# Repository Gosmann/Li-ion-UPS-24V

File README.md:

# Li-ion-UPS-24V

24V-input 24V-out lithium ion uninterruptible power supply

24V -> BUCK LM2596 -> 5V

5V -> Li-ion charger -> 3.7V

3.7V -> BOOST MT3608 -> 24V

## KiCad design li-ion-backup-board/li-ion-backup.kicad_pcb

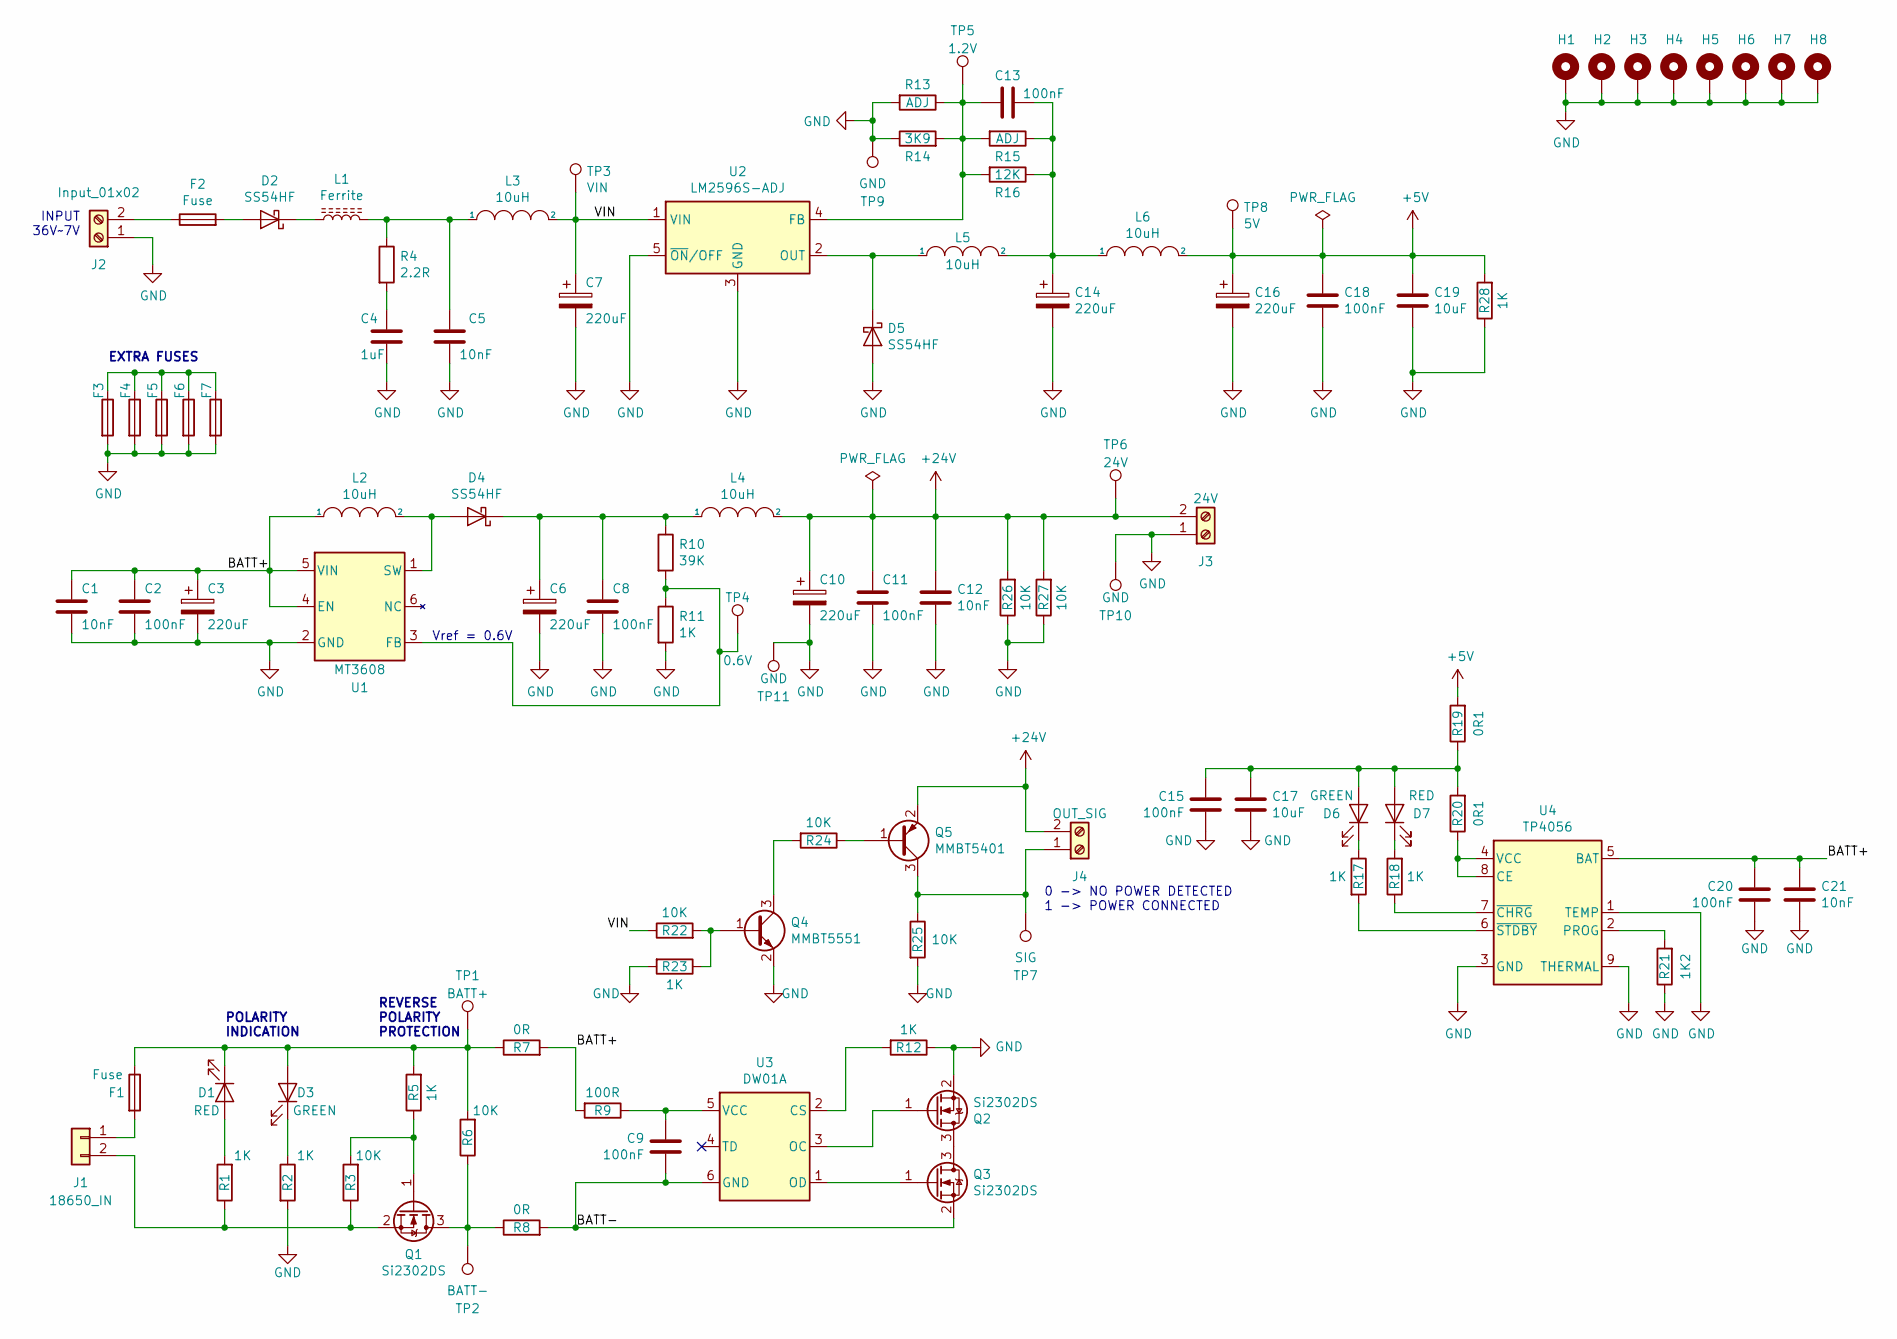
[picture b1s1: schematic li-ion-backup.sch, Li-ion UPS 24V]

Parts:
C1, C5, C12, C21: 10nF; C_0805_2012Metric; LCSC C1710
C2, C8, C9, C11, C13, C15, C18, C20: 100nF; C_0805_2012Metric; Voltage 50V; LCSC C49678
C3, C6, C7, C10, C14, C16: 220uF; CP_Elec_8x10; Voltage 35V; LCSC C311611
C4: 1uF; C_0805_2012Metric; LCSC C28323
C17, C19: 10uF; C_0805_2012Metric; Voltage 25V; LCSC C15850
D1, D7: RED; LED_0805_2012Metric; LCSC C84256
D2, D4, D5: SS54HF; DO-214AC; LCSC C22452
D3, D6: GREEN; LED_0805_2012Metric; LCSC C2297
F1, F2, F3, F4, F5, F6, F7: Fuse; FUSE_1206_3216Metric; LCSC C182445
H1, H2, H3, H4, H5, H6, H7, H8: MountingHole_Pad; MountingHole_3.2mm_M3_Pad_Via
J1: 18650_IN; BatteryHolder_1x18650
J2: Input_01x02; TerminalBlock_Phoenix_MKDS-1,5-2_1x02_P5.08mm_Horizontal_3D
J3: 24V; TerminalBlock_Phoenix_MKDS-1,5-2_1x02_P5.08mm_Horizontal_3D
J4: OUT_SIG; TerminalBlock_Phoenix_MKDS-1,5-2_1x02_P5.08mm_Horizontal_3D
L1: Ferrite; FB_0603_1608Metric; LCSC C1002
L2, L3, L4, L5, L6: 10uH; L_10.4x10.4_H4.8; LCSC C9935
Q1, Q2, Q3: Si2302DS; SOT-23; LCSC C558245
Q4: MMBT5551; SOT-23; LCSC C2145
Q5: MMBT5401; SOT-23; LCSC C8326
R1, R2, R5, R11, R12, R17, R18, R23, R28: 1K; R_0805_2012Metric; LCSC C17513
R3, R6, R22, R24, R25, R26, R27: 10K; R_0805_2012Metric; LCSC C17414
R4: 2.2R; R_0805_2012Metric; LCSC C17521
R7, R8: 0R; R_0805_2012Metric; LCSC C17477
R9: 100R; R_0805_2012Metric; LCSC C17408
R10: 39K; R_0805_2012Metric; LCSC C25826
R13, R15: ADJ; R_0805_2012Metric
R14: 3K9; R_0805_2012Metric; LCSC C17614
R16: 12K; R_0805_2012Metric; LCSC C17444
R19, R20: 0R1; R_1206_3216Metric; LCSC C25334
R21: 1K2; R_0805_2012Metric; LCSC C17379
TP1: BATT+; TestPoint_Pad_D1.0mm
TP2: BATT-; TestPoint_Pad_D1.0mm
TP3: VIN; TestPoint_Pad_D1.0mm
TP4: 0.6V; TestPoint_Pad_D1.0mm
TP5: 1.2V; TestPoint_Pad_D1.0mm
TP6: 24V; TestPoint_Pad_D1.0mm
TP7: SIG; TestPoint_Pad_D1.0mm
TP8: 5V; TestPoint_Pad_D1.0mm
TP9, TP10, TP11: GND; TestPoint_Pad_D1.0mm
U1: MT3608; SOT-23-6; LCSC C84817
U2: LM2596S-ADJ; TO-263-5_TabPin3; LCSC C99046
U3: DW01A; SOT-23-6; LCSC C61503
U4: TP4056; ESOP-8-1EP_3.9x4.9mm_P1.27mm_EP2.41x3.81mm_ThermalVias; LCSC C16581

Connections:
+5V: C16.1, C18.1, C19.1, L6.2, R19.2, R28.2, TP8.1
+24V: C10.1, C11.1, C12.1, J3.2, J4.2, L4.2, Q5.2 (E), R26.2, R27.2, TP6.1
/BATT+: C1.1, C2.1, C3.1, C20.2, C21.1, L2.1, R7.2, R9.2, U1.4 (EN), U1.5 (VIN), U4.5 (BAT)
/BATT-: C9.2, Q3.2 (S), R8.2, U3.6 (GND)
/VIN: C7.1, L3.2, R22.1, TP3.1, U2.1 (VIN)
GND: C1.2, C2.2, C3.2, C4.2, C5.2, C6.2, C7.2, C8.2, C10.2, C11.2, C12.2, C14.2, C15.1, C16.2, C17.2, C18.2, C19.2, C20.1, C21.2, D5.2 (A), F3.2, F4.2, F5.2, F6.2, F7.2, H1.1, H2.1, H3.1, H4.1, H5.1, H6.1, H7.1, H8.1, J2.1, J3.1, Q2.2 (S), Q4.2 (E), R2.2, R11.2, R12.1, R13.2, R14.1, R21.1, R23.2, R25.2, R26.1, R27.1, R28.1, TP9.1, TP10.1, TP11.1, U1.2 (GND), U2.3 (GND), U2.5 (~ON~/OFF), U4.1 (TEMP), U4.3 (GND), U4.9 (THERMAL)
unnamed: C4.1, R4.2
unnamed: C5.1, L1.2, L3.1, R4.1
unnamed: C6.1, C8.1, D4.1 (K), L4.1, R10.1
unnamed: C9.1, R9.1, U3.5 (VCC)
unnamed: C13.1, C14.1, L5.2, L6.1, R15.1, R16.1
unnamed: C13.2, R13.1, R14.2, R15.2, R16.2, TP5.1, U2.4 (FB)
unnamed: C15.2, C17.1, D6.2 (A), D7.2 (A), R19.1, R20.2
unnamed: D1.1 (K), D3.2 (A), F1.1, R5.2, R6.2, R7.1, TP1.1
unnamed: D1.2 (A), R1.2
unnamed: D2.1 (K), L1.1
unnamed: D2.2 (A), F2.2
unnamed: D3.1 (K), R2.1
unnamed: D4.2 (A), L2.2, U1.1 (SW)
unnamed: D5.1 (K), L5.1, U2.2 (OUT)
unnamed: D6.1 (K), R17.1
unnamed: D7.1 (K), R18.2
unnamed: F1.2, J1.1
unnamed: F2.1, J2.2
unnamed: F3.1, F4.1, F5.1, F6.1, F7.1
unnamed: J1.2, Q1.2 (S), R1.1, R3.1
unnamed: J4.1, Q5.3 (C), R25.1, TP7.1
unnamed: Q1.1 (G), R3.2, R5.1
unnamed: Q1.3 (D), R6.1, R8.1, TP2.1
unnamed: Q2.1 (G), U3.3 (OC)
unnamed: Q2.3 (D), Q3.3 (D)
unnamed: Q3.1 (G), U3.1 (OD)
unnamed: Q4.1 (B), R22.2, R23.1
unnamed: Q4.3 (C), R24.2
unnamed: Q5.1 (B), R24.1
unnamed: R10.2, R11.1, TP4.1, U1.3 (FB)
unnamed: R12.2, U3.2 (CS)
unnamed: R17.2, U4.6 (~STDBY)
unnamed: R18.1, U4.7 (~CHRG)
unnamed: R20.1, U4.4 (VCC), U4.8 (CE)
unnamed: R21.2, U4.2 (PROG)

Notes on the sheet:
INPUT 36V~~7V
POLARITY INDICATION
REVERSE POLARITY PROTECTION
Vref = 0.6V
EXTRA FUSES
0 -> NO POWER DETECTED 1 -> POWER CONNECTED

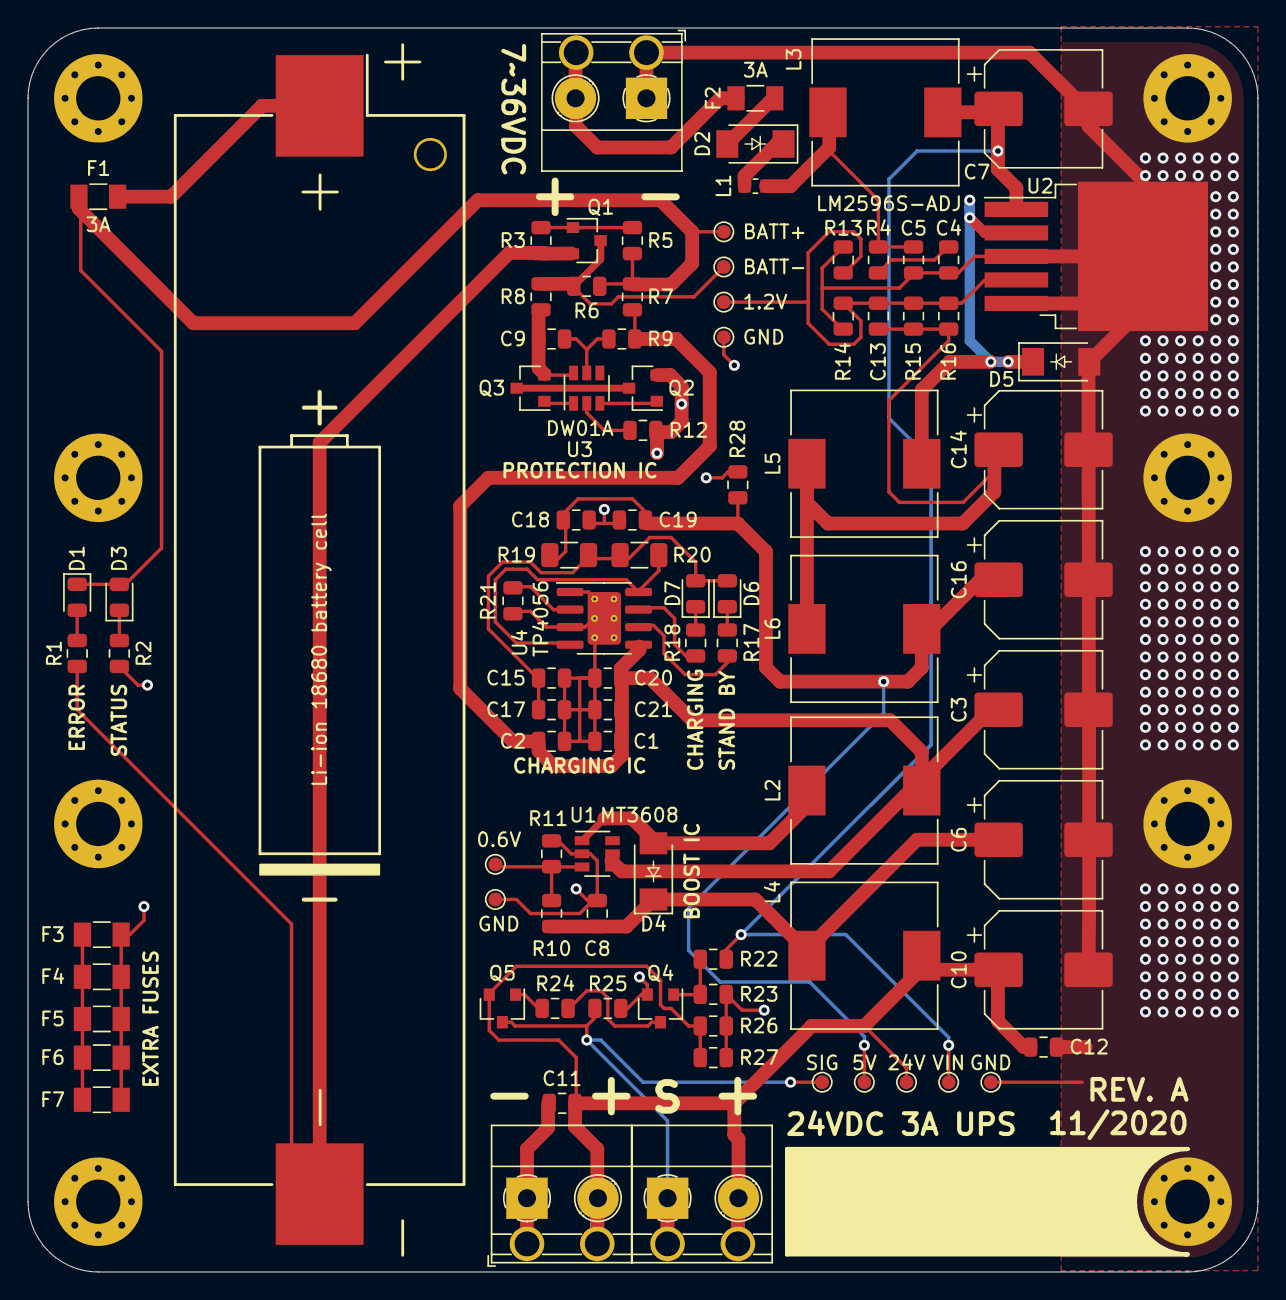
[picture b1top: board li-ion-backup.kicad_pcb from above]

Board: 2 copper layers, 88.9 x 89.9 mm, 101 parts (0 on the bottom side), 41 nets.

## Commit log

2020-10-04 esquematico inicial feito
2020-10-14 update components value
2020-10-14 correcoes de commits com errors
2020-10-14 problema resolvido
2020-10-20 edge cuts corrigido
2020-11-04 add gerbers and production files
2020-11-04 update gerbers folder
2020-12-11 adicionei o olá
2021-06-07 teste
